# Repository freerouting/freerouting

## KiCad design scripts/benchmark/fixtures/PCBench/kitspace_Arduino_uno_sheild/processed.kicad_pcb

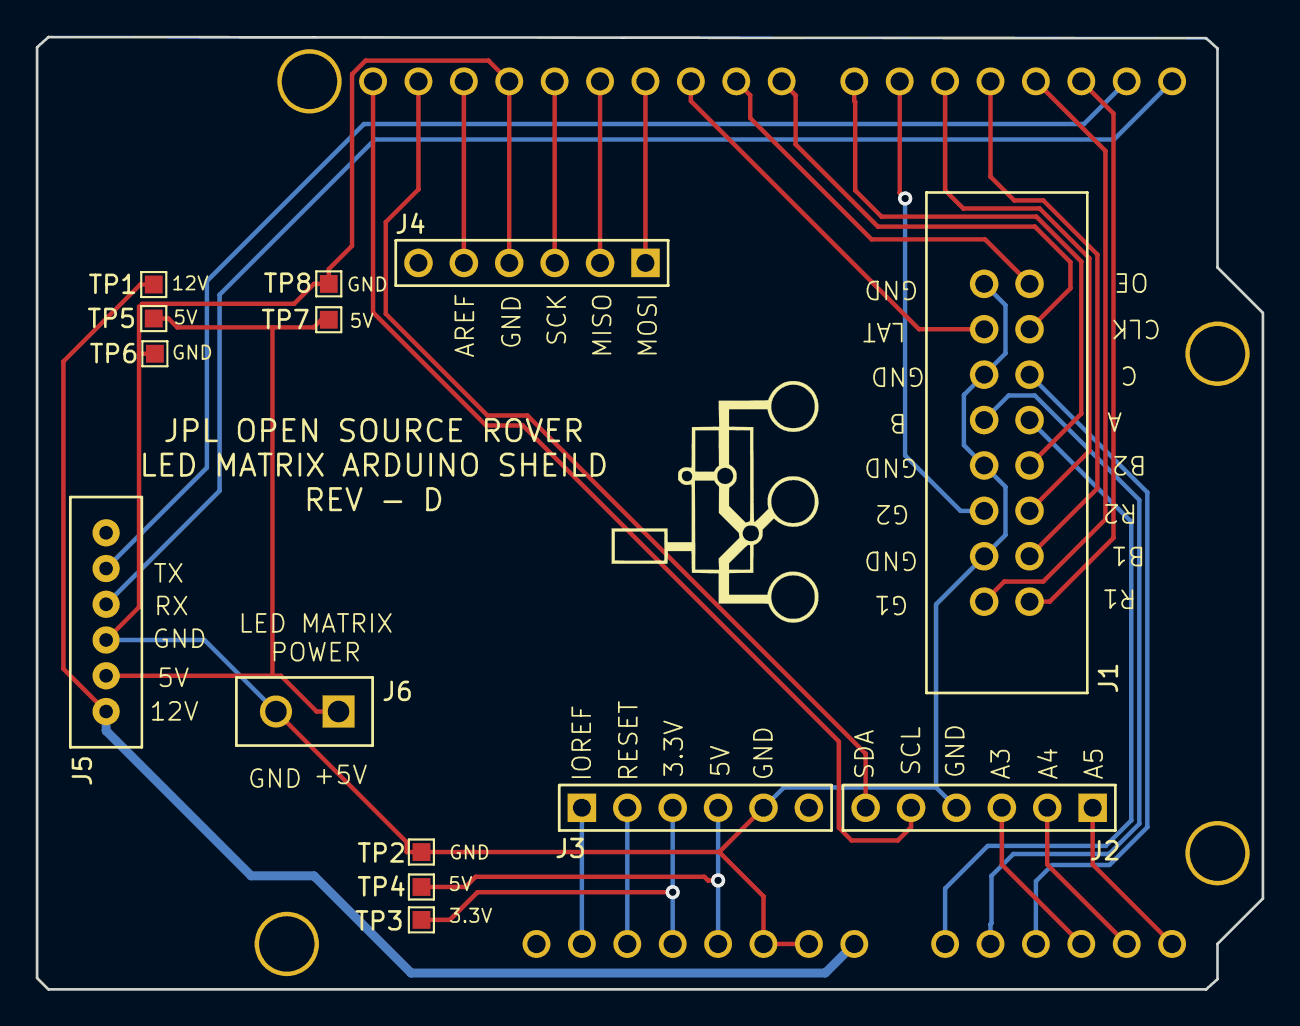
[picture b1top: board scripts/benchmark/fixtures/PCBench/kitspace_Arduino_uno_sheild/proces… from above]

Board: 2 copper layers, 68.6 x 53.3 mm, 16 parts (0 on the bottom side), 30 nets.

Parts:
A1: Arduino_UNO_R3; Arduino Uno Sheild
J1: ED10523-ND; 16 pos 3M connector
J2, J3, J4: 6posheader; 6 pos header pin
J5: 6posheader; 455-1708-ND
J6: ED2580-ND; ED1501-ND
TP1, TP2, TP3, TP4, TP5, TP6, TP7, TP8: TestPoint; TestPoint_Pad_1.0x1.0mm
y1: rover_silkscreen; rover_image

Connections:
+5V: J5.2, J6.1, TP5.1, TP7.1
+12V: A1.26, J5.1, TP1.1
/3.3V: A1.22, J3.3, TP3.1
/5V: A1.23, J3.4, TP4.1
/A: A1.14, J1.9
/A3: A1.17, J2.3
/A4: A1.18, J2.2
/A5: A1.19, J2.1
/AREF: A1.28, J4.5
/B: A1.15, J1.10
/B1: A1.4, J1.3
/B2: A1.7, J1.7
/C: A1.16, J1.11
/CLK: A1.8, J1.13
/G1: A1.3, J1.2
/G2: A1.6, J1.6
/IOREF: A1.20, J3.1
/LAT: A1.10, J1.14
/MISO: A1.12, J4.2
/MOSI: A1.11, J4.1
/OE: A1.9, J1.15
/R1: A1.2, J1.1
/R2: A1.5, J1.5
/RESET: A1.21, J3.2
/RX: A1.0, J5.4
/SCK: A1.13, J4.3
/SCL: A1.30, J2.5
/SDA: A1.29, J2.6
/TX: A1.1, J5.5
GND: A1.24, A1.25, A1.27, J1.4, J1.8, J1.12, J1.16, J2.4, J3.5, J4.4, J5.3, J6.2, TP2.1, TP6.1, TP8.1

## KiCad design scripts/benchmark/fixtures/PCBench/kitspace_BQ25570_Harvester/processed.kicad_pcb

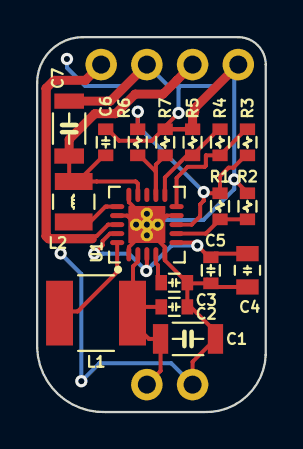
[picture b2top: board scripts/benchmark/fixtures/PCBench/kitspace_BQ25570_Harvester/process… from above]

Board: 2 copper layers, 12.7 x 20.8 mm, 20 parts (0 on the bottom side), 13 nets.

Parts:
C1, C7: 22uF; 3216_B
C2, C5, C6: 0.1uF; 1608_B
C3: 10nF; 1608_B
C4: 4.7uF; 2012_B
L1: 22uH; Abracon_ASPI-0418FS
L2: 10uH; 2520_B
P1: INPUT; JP-2
P2: LIPO; JP-2
P3: LOAD; JP-2
R1: 7.87M; 1608_B
R2: 6.04M; 1608_B
R3: 0.698M; 1608_B
R4: 8.06M; 1608_B
R5: 4.22M; 1608_B
R6: 6.65M; 1608_B
R7: 6.19M; 1608_B
U1: TI_BQ25570; QFN-20-TE

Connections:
+BATT: P2.1, U1.18
/VIN: C1.1, C2.1, L1.1, P1.1, U1.2
/VOUT: C6.1, C7.1, L2.2, P3.1, U1.14
GND: C1.2, C2.2, C3.2, C4.2, C5.2, C6.2, C7.2, P1.2, P2.2, P3.2, R2.2, R5.2, R7.2, U1.1, U1.5, U1.9, U1.15, U1.17, U1.21
unnamed: C3.1, U1.4
unnamed: C4.1, C5.1, U1.3, U1.6, U1.19
unnamed: L1.2, U1.20
unnamed: L2.1, U1.16
unnamed: R1.1, R3.1, R6.1, U1.8
unnamed: R1.2, R2.1, U1.7
unnamed: R3.2, R4.1, U1.10
unnamed: R4.2, R5.1, U1.11
unnamed: R6.2, R7.1, U1.12

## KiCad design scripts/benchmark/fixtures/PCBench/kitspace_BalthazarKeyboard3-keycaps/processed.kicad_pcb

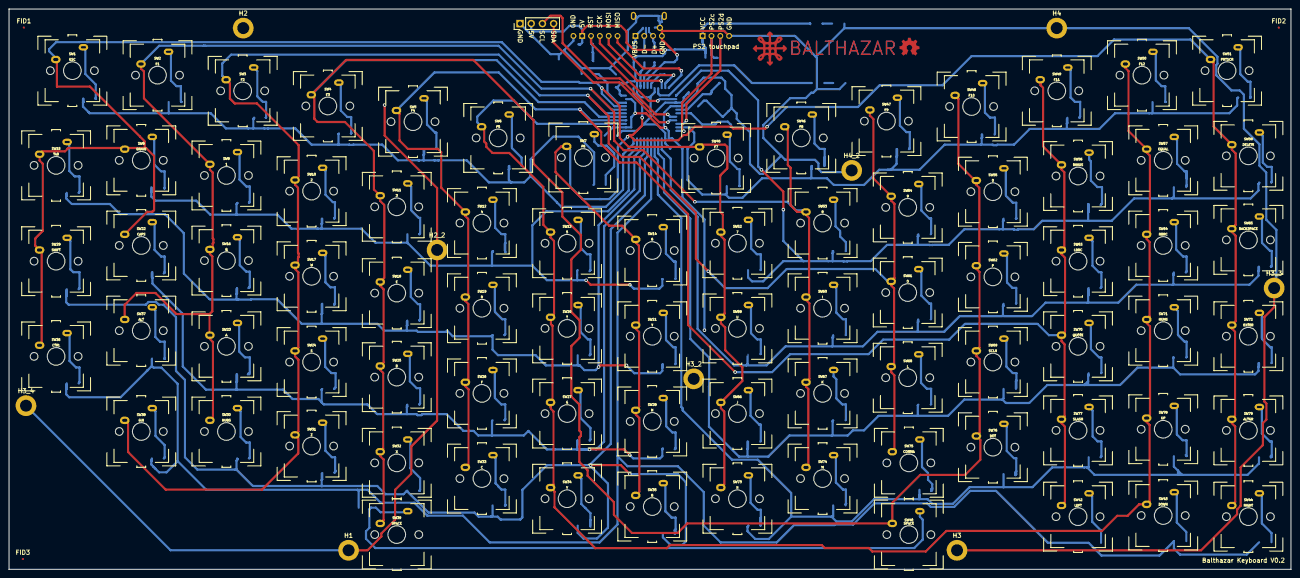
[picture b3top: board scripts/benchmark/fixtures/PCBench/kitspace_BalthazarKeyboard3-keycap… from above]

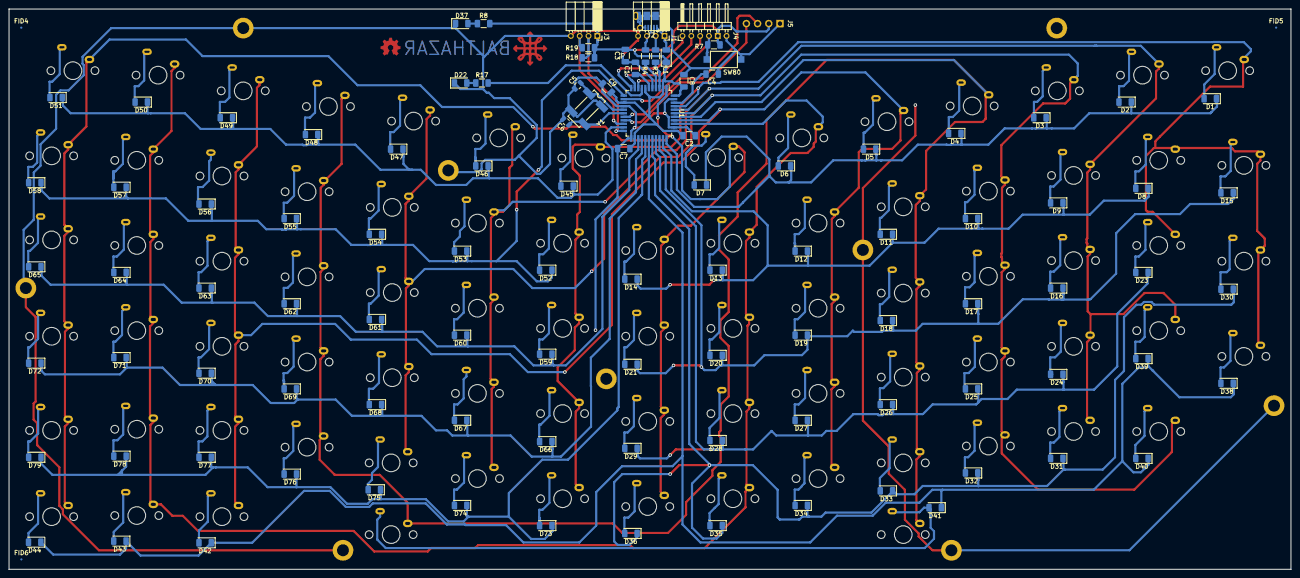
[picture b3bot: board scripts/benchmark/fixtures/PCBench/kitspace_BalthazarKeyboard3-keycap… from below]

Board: 4 copper layers, 290.6 x 127.0 mm, 197 parts (106 on the bottom side), 117 nets.

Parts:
C1: 1uF; C_1206_3216Metric
C2: 10uF; C_1206_3216Metric
C3, C4, C7, C8, C9: 0.1uF; C_1206_3216Metric
C5, C6: 22pF; C_0805_2012Metric
D1, D2, D3, D4, D5, D6, D7, D8, D9, D10, D11, D12, D13, D14, D15, D16, D17, D18, D19, D20, D21, D23, D24, D25, D26, D27, D28, D29, D30, D31, D32, D33, D34, D35, D36, D38, D39, D40, D41, D42, D43, D44, D45, D46, D47, D48, D49, D50, D51, D52, D53, D54, D55, D56, D57, D58, D59, D60, D61, D62, D63, D64, D65, D66, D67, D68, D69, D70, D71, D72, D73, D74, D75, D76, D77, D78, D79: D; D_1206_3216Metric
D22, D37: LED_Small; LED_1206_3216Metric
FID1, FID2, FID3, FID4, FID5, FID6: Fiducial; Fiducial_0.5mm_Mask1mm
H1, H2, H2_2, H3, H3_2, H3_3, H3_4, H4, H4_2: MountingHole_Pad; MountingHole_2.7mm_M2.5_DIN965_Pad
J1: USB; PinSocket_1x04_P2.00mm_Horizontal
J2: USB_B_Micro; USB_Micro-B_Molex-Balthazar
J3: PS2 touchpad; PinSocket_1x04_P2.00mm_Horizontal
J4: ISP; PinHeader_1x06_P2.00mm_Horizontal
J5: I2C; PinHeader_1x04_P2.54mm_Vertical
L1: L_Core_Ferrite_Small; D_1206_3216Metric
R3, R4: 22; R_1206_3216Metric
R7, R18, R19: 10K; R_1206_3216Metric
R8, R17: 200; R_1206_3216Metric
SW1: ESC; CherryMX_RGB_SpeedSilver
SW2: F1; CherryMX_RGB_SpeedSilver
SW3: F2; CherryMX_RGB_SpeedSilver
SW4: F3; CherryMX_RGB_SpeedSilver
SW5: F4; CherryMX_RGB_SpeedSilver
SW6: F5; CherryMX_RGB_SpeedSilver
SW7: F6; CherryMX_RGB_SpeedSilver
SW8: GRAVE; CherryMX_RGB_SpeedSilver
SW9: 1; CherryMX_RGB_SpeedSilver
SW10: 2; CherryMX_RGB_SpeedSilver
SW11: 3; CherryMX_RGB_SpeedSilver
SW12: 4; CherryMX_RGB_SpeedSilver
SW13: 5; CherryMX_RGB_SpeedSilver
SW14: 6; CherryMX_RGB_SpeedSilver
SW15: TAB; CherryMX_RGB_SpeedSilver
SW16: Q; CherryMX_RGB_SpeedSilver
SW17: W; CherryMX_RGB_SpeedSilver
SW18: E; CherryMX_RGB_SpeedSilver
SW19: R; CherryMX_RGB_SpeedSilver
SW20: T; CherryMX_RGB_SpeedSilver
SW21: Y; CherryMX_RGB_SpeedSilver
SW22: CAPS; CherryMX_RGB_SpeedSilver
SW23: A; CherryMX_RGB_SpeedSilver
SW24: S; CherryMX_RGB_SpeedSilver
SW25: D; CherryMX_RGB_SpeedSilver
SW26: F; CherryMX_RGB_SpeedSilver
SW27: G; CherryMX_RGB_SpeedSilver
SW28: H; CherryMX_RGB_SpeedSilver
SW29: SHIFT; CherryMX_RGB_SpeedSilver
SW30: NUBS; CherryMX_RGB_SpeedSilver
SW31: Z; CherryMX_RGB_SpeedSilver
SW32: X; CherryMX_RGB_SpeedSilver
SW33: C; CherryMX_RGB_SpeedSilver
SW34: V; CherryMX_RGB_SpeedSilver
SW35: B; CherryMX_RGB_SpeedSilver
SW36: CTRL; CherryMX_RGB_SpeedSilver
SW37: ALT; CherryMX_RGB_SpeedSilver
SW38: GUI; CherryMX_RGB_SpeedSilver
SW39, SW40: SPACE; CherryMX_RGB_SpeedSilver
SW42: LEFT; CherryMX_RGB_SpeedSilver
SW43: DOWN; CherryMX_RGB_SpeedSilver
SW44: RIGHT; CherryMX_RGB_SpeedSilver
SW45: F7; CherryMX_RGB_SpeedSilver
SW46: F8; CherryMX_RGB_SpeedSilver
SW47: F9; CherryMX_RGB_SpeedSilver
SW48: F10; CherryMX_RGB_SpeedSilver
SW49: F11; CherryMX_RGB_SpeedSilver
SW50: F12; CherryMX_RGB_SpeedSilver
SW51: PRTSCR; CherryMX_RGB_SpeedSilver
SW52: 7; CherryMX_RGB_SpeedSilver
SW53: 8; CherryMX_RGB_SpeedSilver
SW54: 9; CherryMX_RGB_SpeedSilver
SW55: 0; CherryMX_RGB_SpeedSilver
SW56: MINUS; CherryMX_RGB_SpeedSilver
SW57: EQUAL; CherryMX_RGB_SpeedSilver
SW58: DELETE; CherryMX_RGB_SpeedSilver
SW59: U; CherryMX_RGB_SpeedSilver
SW60: I; CherryMX_RGB_SpeedSilver
SW61: O; CherryMX_RGB_SpeedSilver
SW62: P; CherryMX_RGB_SpeedSilver
SW63: LBRC; CherryMX_RGB_SpeedSilver
SW64: RBRC; CherryMX_RGB_SpeedSilver
SW65: BACKSPACE; CherryMX_RGB_SpeedSilver
SW66: J; CherryMX_RGB_SpeedSilver
SW67: K; CherryMX_RGB_SpeedSilver
SW68: L; CherryMX_RGB_SpeedSilver
SW69: SCLN; CherryMX_RGB_SpeedSilver
SW70: QUOTE; CherryMX_RGB_SpeedSilver
SW71: NUHS; CherryMX_RGB_SpeedSilver
SW72: ENTER; CherryMX_RGB_SpeedSilver
SW73: N; CherryMX_RGB_SpeedSilver
SW74: M; CherryMX_RGB_SpeedSilver
SW75: COMMA; CherryMX_RGB_SpeedSilver
SW76: DOT; CherryMX_RGB_SpeedSilver
SW77: SLASH; CherryMX_RGB_SpeedSilver
SW78: UP; CherryMX_RGB_SpeedSilver
SW79: ALTGR; CherryMX_RGB_SpeedSilver
SW80: SW_Push; SW_SPST_CK_RS282G05A3
U1: ATmega32U4_Balthazar; TQFP-44_10x10mm_P0.8mm
Y1: Crystal_16M; Crystal_SMD_SeikoEpson_MC306-4Pin_8.0x3.2mm_HandSoldering

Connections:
GND: C1.2, C2.1, C3.1, C4.2, C5.2, C6.2, C7.1, C8.1, C9.1, D22.1, D37.1, H1.1, H2.1, H2_2.1, H3.1, H3_2.1, H3_3.1, H3_4.1, H4.1, H4_2.1, J1.4, J2.5, J2.6, J3.4, J4.6, J5.1, SW80.1, U1.5, U1.15, U1.23, U1.35, U1.43, Y1.2, Y1.4
unnamed: C1.1, U1.6
unnamed: C4.1, U1.42
unnamed: C5.1, U1.16, Y1.1
unnamed: C6.1, U1.17, Y1.3
unnamed: D1.2, SW1.2
unnamed: D2.2, SW2.2
unnamed: D3.2, SW3.2
unnamed: D4.2, SW4.2
unnamed: D5.2, SW5.2
unnamed: D6.2, SW6.2
unnamed: D7.2, SW7.2
unnamed: D8.2, SW8.2
unnamed: D9.2, SW9.2
unnamed: D10.2, SW10.2
unnamed: D11.2, SW11.2
unnamed: D12.2, SW12.2
unnamed: D13.2, SW13.2
unnamed: D14.2, SW14.2
unnamed: D15.2, SW15.2
unnamed: D16.2, SW16.2
unnamed: D17.2, SW17.2
unnamed: D18.2, SW18.2
unnamed: D19.2, SW19.2
unnamed: D20.2, SW20.2
unnamed: D21.2, SW21.2
unnamed: D22.2, R17.1
unnamed: D23.2, SW22.2
unnamed: D24.2, SW23.2
unnamed: D25.2, SW24.2
unnamed: D26.2, SW25.2
unnamed: D27.2, SW26.2
unnamed: D28.2, SW27.2
unnamed: D29.2, SW28.2
unnamed: D30.2, SW29.2
unnamed: D31.2, SW30.2
unnamed: D32.2, SW31.2
unnamed: D33.2, SW32.2
unnamed: D34.2, SW33.2
unnamed: D35.2, SW34.2
unnamed: D36.2, SW35.2
unnamed: D37.2, R8.1
unnamed: D38.2, SW36.2
unnamed: D39.2, SW37.2
unnamed: D40.2, SW38.2
unnamed: D41.2, SW39.2, SW40.2
unnamed: D42.2, SW42.2
unnamed: D43.2, SW43.2
unnamed: D44.2, SW44.2
unnamed: D45.2, SW45.2
unnamed: D46.2, SW46.2
unnamed: D47.2, SW47.2
unnamed: D48.2, SW48.2
unnamed: D49.2, SW49.2
unnamed: D50.2, SW50.2
unnamed: D51.2, SW51.2
unnamed: D52.2, SW52.2
unnamed: D53.2, SW53.2
unnamed: D54.2, SW54.2
unnamed: D55.2, SW55.2
unnamed: D56.2, SW56.2
unnamed: D57.2, SW57.2
unnamed: D58.2, SW58.2
unnamed: D59.2, SW59.2
unnamed: D60.2, SW60.2
unnamed: D61.2, SW61.2
unnamed: D62.2, SW62.2
unnamed: D63.2, SW63.2
unnamed: D64.2, SW64.2
unnamed: D65.2, SW65.2
unnamed: D66.2, SW66.2
unnamed: D67.2, SW67.2
unnamed: D68.2, SW68.2
unnamed: D69.2, SW69.2
unnamed: D70.2, SW70.2
unnamed: D71.2, SW71.2
unnamed: D72.2, SW72.2
unnamed: D73.2, SW73.2
unnamed: D74.2, SW74.2
unnamed: D75.2, SW75.2
unnamed: D76.2, SW76.2
unnamed: D77.2, SW77.2
unnamed: D78.2, SW78.2
unnamed: D79.2, SW79.2
unnamed: J1.1, J2.1, L1.2
unnamed: J1.2, J2.2, R3.1
unnamed: J1.3, J2.3, R4.1
unnamed: J4.1, U1.11
unnamed: J4.2, U1.10
unnamed: J4.3, U1.9
unnamed: J5.3, U1.18
unnamed: J5.4, U1.19
unnamed: R3.2, U1.3
unnamed: R4.2, U1.4
unnamed: R17.2, U1.8
PS2clock: J3.2, R18.2, U1.22
PS2data: J3.3, R19.2, U1.20
RST: J4.4, R7.2, SW80.2, U1.13
Vcc: C2.2, C3.2, C7.2, C8.2, C9.2, J3.1, J4.5, J5.2, L1.1, R7.1, R8.2, R18.1, R19.1, U1.2, U1.7, U1.14, U1.24, U1.34, U1.44
col1: D1.1, D2.1, D3.1, D4.1, D5.1, D6.1, D7.1, U1.33
col2: D8.1, D9.1, D10.1, D11.1, D12.1, D13.1, D14.1, U1.32
col3: D15.1, D16.1, D17.1, D18.1, D19.1, D20.1, D21.1, U1.31
col4: D23.1, D24.1, D25.1, D26.1, D27.1, D28.1, D29.1, U1.30
col5: D30.1, D31.1, D32.1, D33.1, D34.1, D35.1, D36.1, U1.29
col6: D38.1, D39.1, D40.1, D41.1, D42.1, D43.1, D44.1, U1.28
col7: D73.1, D74.1, D75.1, D76.1, D77.1, D78.1, D79.1, U1.27
col8: D66.1, D67.1, D68.1, D69.1, D70.1, D71.1, D72.1, U1.26
col9: D59.1, D60.1, D61.1, D62.1, D63.1, D64.1, D65.1, U1.25
col10: D52.1, D53.1, D54.1, D55.1, D56.1, D57.1, D58.1, U1.12
col11: D45.1, D46.1, D47.1, D48.1, D49.1, D50.1, D51.1, U1.21
row1: SW1.1, SW8.1, SW15.1, SW22.1, SW29.1, SW36.1, SW45.1, SW52.1, SW59.1, SW66.1, SW73.1, U1.41
row2: SW2.1, SW9.1, SW16.1, SW23.1, SW30.1, SW37.1, SW46.1, SW53.1, SW60.1, SW67.1, SW74.1, U1.40
row3: SW3.1, SW10.1, SW17.1, SW24.1, SW31.1, SW38.1, SW47.1, SW54.1, SW61.1, SW68.1, SW75.1, U1.39
row4: SW4.1, SW11.1, SW18.1, SW25.1, SW32.1, SW39.1, SW40.1, SW48.1, SW55.1, SW62.1, SW69.1, SW76.1, U1.38
row5: SW5.1, SW12.1, SW19.1, SW26.1, SW33.1, SW42.1, SW49.1, SW56.1, SW63.1, SW70.1, SW77.1, U1.37
row6: SW6.1, SW13.1, SW20.1, SW27.1, SW34.1, SW43.1, SW50.1, SW57.1, SW64.1, SW71.1, SW78.1, U1.36
row7: SW7.1, SW14.1, SW21.1, SW28.1, SW35.1, SW44.1, SW51.1, SW58.1, SW65.1, SW72.1, SW79.1, U1.1
